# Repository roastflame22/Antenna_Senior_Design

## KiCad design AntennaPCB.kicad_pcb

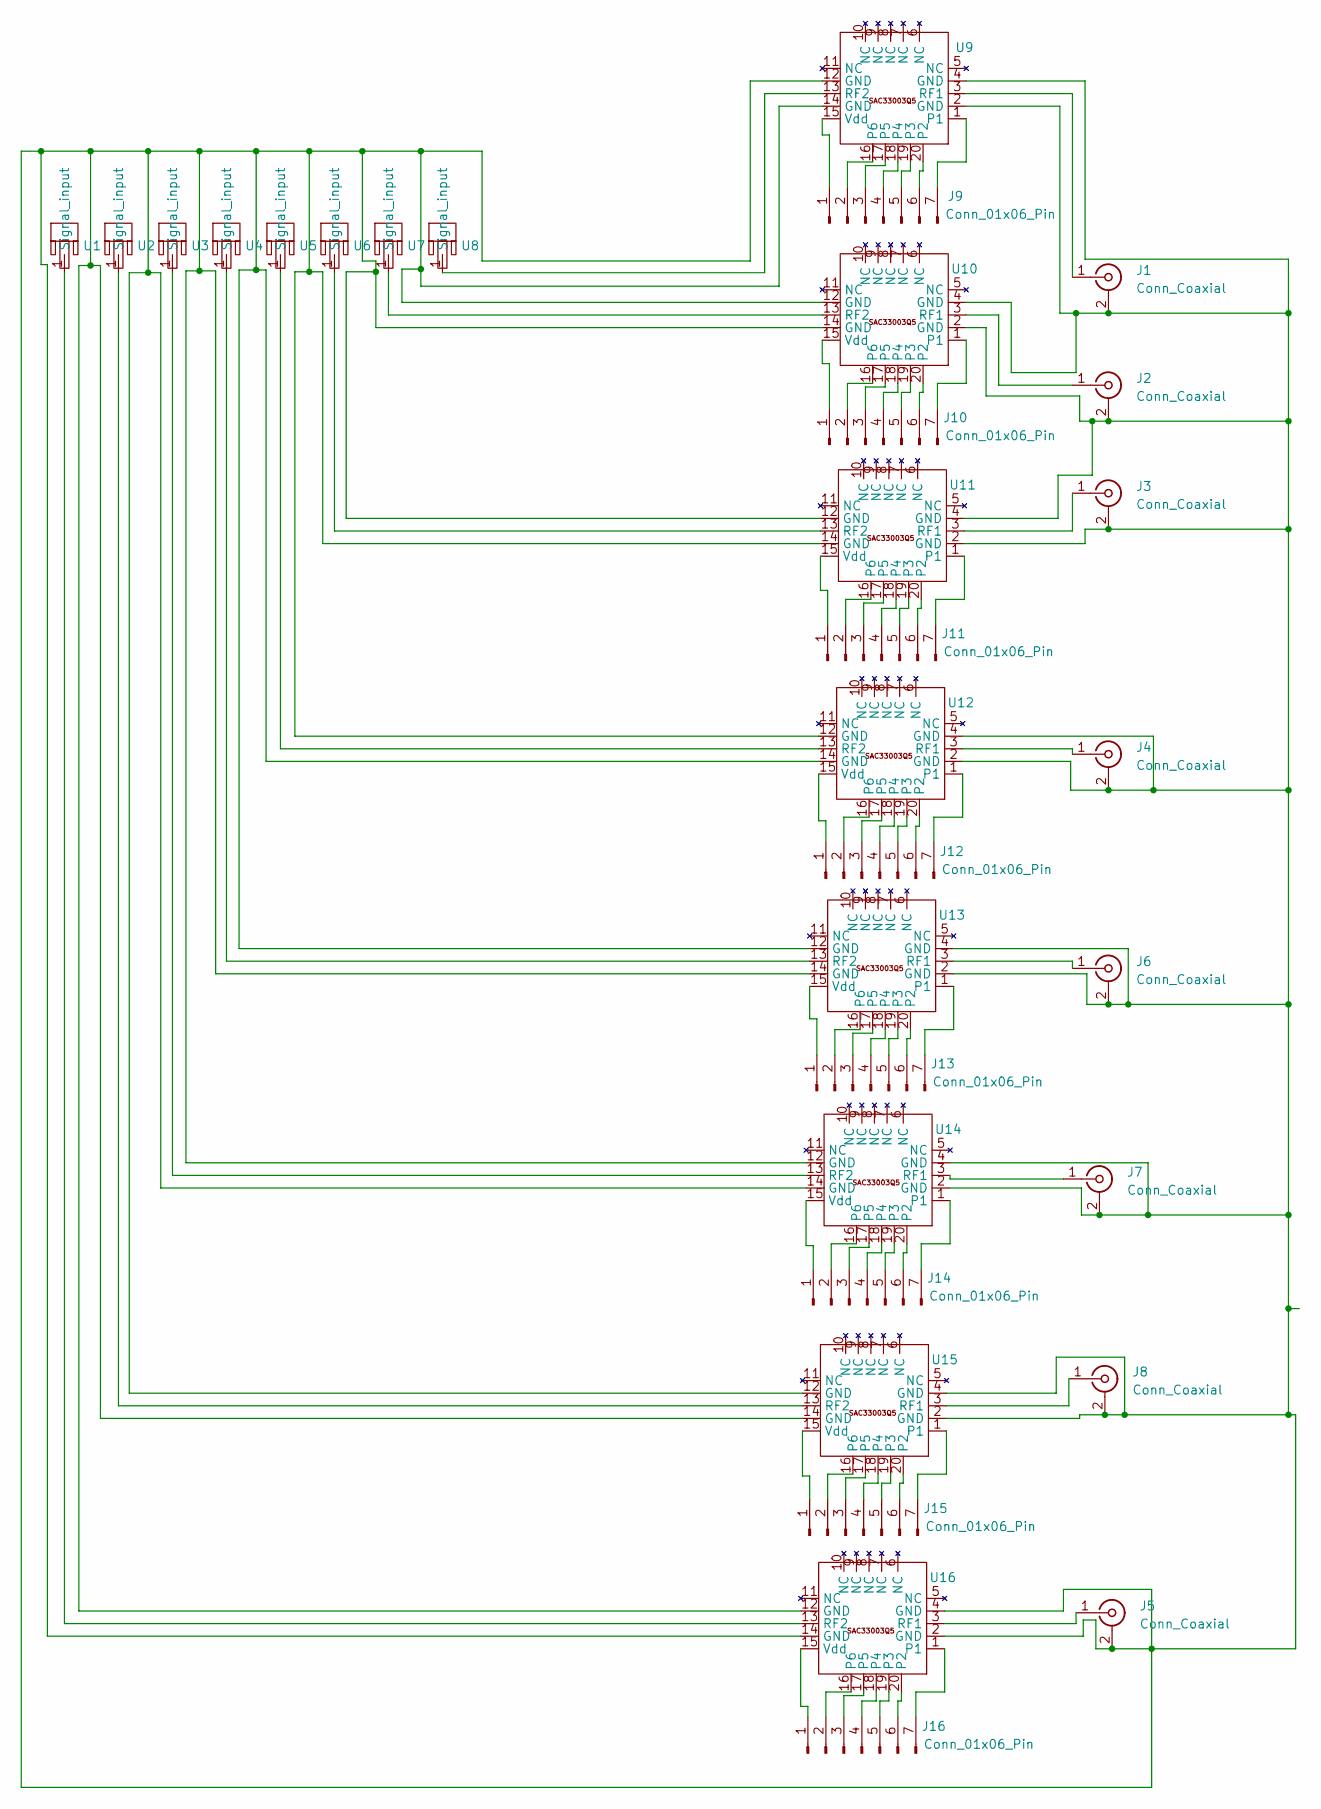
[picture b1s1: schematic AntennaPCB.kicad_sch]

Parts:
J1, J2, J3, J4, J5, J6, J7, J8: Conn_Coaxial; SMA_Molex_73251-1153_EdgeMount_Horizontal
J9, J10, J11, J12, J13, J14, J15, J16: Conn_01x06_Pin; JST_EH_B7B-EH-A_1x07_P2.50mm_Vertical
U1, U2, U3, U4, U5, U6, U7, U8: Antenna element
U9, U10, U11, U12, U13, U14, U15, U16: QFN-20-1EP_5x5mm_P0.65mm_EP3.35x3.35mm

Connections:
unnamed: J1.2 (Ext), J2.2 (Ext), J3.2 (Ext), J4.2 (Ext), J5.2 (Ext), J6.2 (Ext), J7.2 (Ext), J8.2 (Ext), U9.2 (GND), U9.4 (GND), U9.12 (GND), U9.14 (GND), U10.2 (GND), U10.4 (GND), U10.12 (GND), U10.14 (GND), U11.2 (GND), U11.4 (GND), U11.12 (GND), U11.14 (GND), U12.2 (GND), U12.4 (GND), U12.12 (GND), U12.14 (GND), U13.2 (GND), U13.4 (GND), U13.12 (GND), U13.14 (GND), U14.2 (GND), U14.4 (GND), U14.12 (GND), U14.14 (GND), U15.2 (GND), U15.4 (GND), U15.12 (GND), U15.14 (GND), U16.2 (GND), U16.4 (GND), U16.12 (GND), U16.14 (GND)
unnamed: J1.1 (In), U9.3 (RF1)
unnamed: J2.1 (In), U10.3 (RF1)
unnamed: J3.1 (In), U11.3 (RF1)
unnamed: J4.1 (In), U12.3 (RF1)
unnamed: J5.1 (In), U16.3 (RF1)
unnamed: J6.1 (In), U13.3 (RF1)
unnamed: J7.1 (In), U14.3 (RF1)
unnamed: J8.1 (In), U15.3 (RF1)
unnamed: J9.1, U9.15 (Vdd)
unnamed: J9.2, U9.16 (P6)
unnamed: J9.3, U9.17 (P5)
unnamed: J9.4, U9.18 (P4)
unnamed: J9.5, U9.19 (P3)
unnamed: J9.6, U9.20 (P2)
unnamed: J9.7, U9.1
unnamed: J10.1, U10.15 (Vdd)
unnamed: J10.2, U10.16 (P6)
unnamed: J10.3, U10.17 (P5)
unnamed: J10.4, U10.18 (P4)
unnamed: J10.5, U10.19 (P3)
unnamed: J10.6, U10.20 (P2)
unnamed: J10.7, U10.1
unnamed: J11.1, U11.15 (Vdd)
unnamed: J11.2, U11.16 (P6)
unnamed: J11.3, U11.17 (P5)
unnamed: J11.4, U11.18 (P4)
unnamed: J11.5, U11.19 (P3)
unnamed: J11.6, U11.20 (P2)
unnamed: J11.7, U11.1
unnamed: J12.1, U12.15 (Vdd)
unnamed: J12.2, U12.16 (P6)
unnamed: J12.3, U12.17 (P5)
unnamed: J12.4, U12.18 (P4)
unnamed: J12.5, U12.19 (P3)
unnamed: J12.6, U12.20 (P2)
unnamed: J12.7, U12.1
unnamed: J13.1, U13.15 (Vdd)
unnamed: J13.2, U13.16 (P6)
unnamed: J13.3, U13.17 (P5)
unnamed: J13.4, U13.18 (P4)
unnamed: J13.5, U13.19 (P3)
unnamed: J13.6, U13.20 (P2)
unnamed: J13.7, U13.1
unnamed: J14.1, U14.15 (Vdd)
unnamed: J14.2, U14.16 (P6)
unnamed: J14.3, U14.17 (P5)
unnamed: J14.4, U14.18 (P4)
unnamed: J14.5, U14.19 (P3)
unnamed: J14.6, U14.20 (P2)
unnamed: J14.7, U14.1
unnamed: J15.1, U15.15 (Vdd)
unnamed: J15.2, U15.16 (P6)
unnamed: J15.3, U15.17 (P5)
unnamed: J15.4, U15.18 (P4)
unnamed: J15.5, U15.19 (P3)
unnamed: J15.6, U15.20 (P2)
unnamed: J15.7, U15.1
unnamed: J16.1, U16.15 (Vdd)
unnamed: J16.2, U16.16 (P6)
unnamed: J16.3, U16.17 (P5)
unnamed: J16.4, U16.18 (P4)
unnamed: J16.5, U16.19 (P3)
unnamed: J16.6, U16.20 (P2)
unnamed: J16.7, U16.1
unnamed: U1.1 (Signal_input), U16.13 (RF2)
unnamed: U8.1 (Signal_input), U9.13 (RF2)
unnamed: U7.1 (Signal_input), U10.13 (RF2)
unnamed: U6.1 (Signal_input), U11.13 (RF2)
unnamed: U5.1 (Signal_input), U12.13 (RF2)
unnamed: U4.1 (Signal_input), U13.13 (RF2)
unnamed: U3.1 (Signal_input), U14.13 (RF2)
unnamed: U2.1 (Signal_input), U15.13 (RF2)

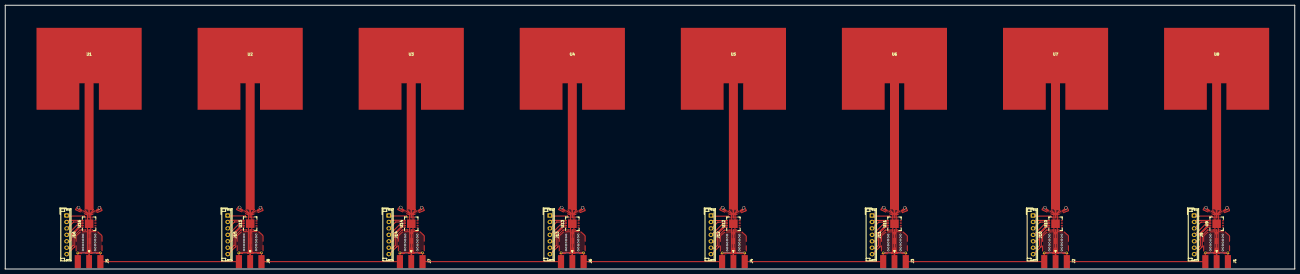
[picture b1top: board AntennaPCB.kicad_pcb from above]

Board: 2 copper layers, 500.3 x 102.3 mm, 32 parts (0 on the bottom side), 73 nets.

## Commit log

2023-12-13 First revision
2023-12-13 Fixed the antenna
